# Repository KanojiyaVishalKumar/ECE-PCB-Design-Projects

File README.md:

# ECE PCB Design Projects

## Overview

Welcome to my PCB Design Projects repository.

This repository contains a collection of electronic circuit and PCB designs created using **KiCad** as part of my learning journey in **Electronics and Communication Engineering (ECE)**.

The goal of these projects is to strengthen my understanding of:

* Schematic design
* PCB layout
* Component selection
* Circuit simulation
* PCB routing
* Power electronics
* Embedded systems
* Hardware design

Most of the projects currently focus on **PCB design and 3D visualization**. Future updates will include PCB fabrication, hardware testing, performance analysis, and design optimization.

---

## Projects

| Status | Project                                |
| ------ | -------------------------------------- |
| ✅      | LM2596 Adjustable Buck Converter       |
| 🔨     | NE555 PWM LED Dimmer (Current Project) |
| 🔊     | LM386 Audio Amplifier                  |
| ⚡      | LM317 Adjustable Power Supply          |
| 🔌     | USB-to-UART Board                      |
| 🌡️    | Temperature Sensor Board               |
| 🖥️    | MCU + OLED Board                       |
| 📡     | ESP32 Sensor/Control Board             |
| 🏆     | Custom ESP32 Development Board         |

---

## Tools and Software

* KiCad
* PCB Editor
* Schematic Editor
* 3D Viewer

---

## Repository Structure

Each project contains:

* Circuit schematic
* PCB layout
* 3D PCB images
* Component information
* Project documentation

---

## Skills Demonstrated

* PCB design
* Analog electronics
* Power electronics
* Embedded systems
* Electronic circuit design
* Component placement
* PCB routing
* Design rule checking (DRC)

---

## Future Goals

* Fabricate the designed PCBs
* Test the hardware
* Improve power efficiency
* Optimize PCB layouts
* Expand the repository with more advanced projects

---

## Connect With Me

I regularly share my electronics projects and learning progress through GitHub and LinkedIn.

Feedback, suggestions, and collaboration are always welcome.

---

**Designed by:**  Kanojiya Vishal Kumar

**Branch:** Electronics and Communication Engineering (ECE)

**Software Used:** KiCad 10.0

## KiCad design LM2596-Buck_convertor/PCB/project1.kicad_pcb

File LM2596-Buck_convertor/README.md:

# LM2596 Adjustable Buck Converter

## Overview

This project presents the PCB design of an **LM2596-based adjustable buck converter** developed using **KiCad**.

A buck converter is a DC-to-DC power converter that efficiently reduces a higher input voltage to a lower output voltage while minimizing power loss. This design focuses on creating a compact, adjustable, and efficient power supply suitable for electronics prototyping and embedded system applications.

---

## Project Objectives

* Design an adjustable DC-DC buck converter
* Develop the complete schematic in KiCad
* Create a compact PCB layout
* Improve PCB routing and component placement skills
* Generate a 3D visualization of the final PCB

---

## Features

* Adjustable output voltage
* High-efficiency DC-to-DC conversion
* Compact PCB design
* Through-hole and standard components
* 3D PCB model

---

## Components Used

* LM2596 switching regulator
* Inductor
* Schottky diode
* Input capacitor
* Output capacitor
* Potentiometer
* Input connector
* Output connector
* Status LED

---

## PCB Design Process

1. Circuit design
2. Schematic capture
3. Footprint assignment
4. Component placement
5. PCB routing
6. Design rule checking (DRC)
7. 3D model generation

---

## Project Files

```text
LM2596-Adjustable-Buck-Converter
│
├── README.md
├── Schematic
├── PCB
└── Images
    ├── Schematic.png
    ├── PCB_Layout.png
    ├── 3D_Front.png
    └── 3D_Back.png
```

---

## Learning Outcomes

This project improved my understanding of:

* Switching regulators
* Power electronics
* PCB design principles
* Component placement
* PCB routing
* Electronic design automation (EDA) tools

---

## Future Improvements

* PCB fabrication
* Hardware testing
* Efficiency analysis
* Thermal analysis
* Design optimization

---

## Software Used

* KiCad

---

**Designed by Kanojiya Vishal Kumar**

**Electronics and Communication Engineering (ECE)**

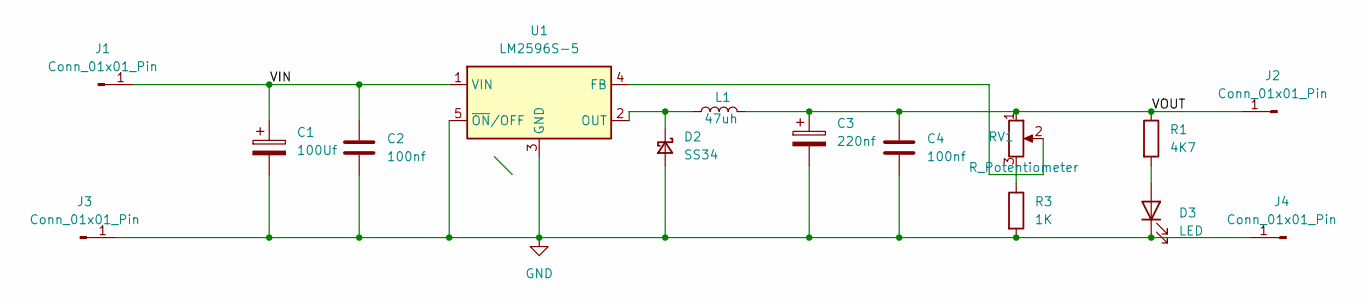
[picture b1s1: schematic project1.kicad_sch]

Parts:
C1: 100Uf; CP_Elec_8x10
C2, C4: 100nf; C_0603_1608Metric
C3: 220nf; CP_Elec_8x10
D2: SS34; D_SMA
D3: LED; LED_0603_1608Metric
J1, J2, J3, J4: Conn_01x01_Pin; PinSocket_1x01_P2.54mm_Vertical
L1: 47uh; L_0805_2012Metric
R1: 4K7; R_0603_1608Metric
R3: 1K; R_0603_1608Metric
RV1: R_Potentiometer; Potentiometer_Bourns_3296Y_Vertical
U1: LM2596S-5; TO-263-5_TabPin3

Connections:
/VIN: C1.1, C2.1, J1.1 (Pin_1_1), U1.1 (VIN)
/VOUT: C3.1, C4.1, J2.1 (Pin_1_1), L1.2, R1.1, RV1.1
GND: C1.2, C2.2, C3.2, C4.2, D2.2 (A), D3.1 (K), J3.1 (Pin_1_1), J4.1 (Pin_1_1), R3.2, U1.3 (GND), U1.5 (~ON/OFF)
unnamed: D2.1 (K), L1.1, U1.2 (OUT)
unnamed: D3.2 (A), R1.2
unnamed: R3.1, RV1.3
unnamed: RV1.2, U1.4 (FB)

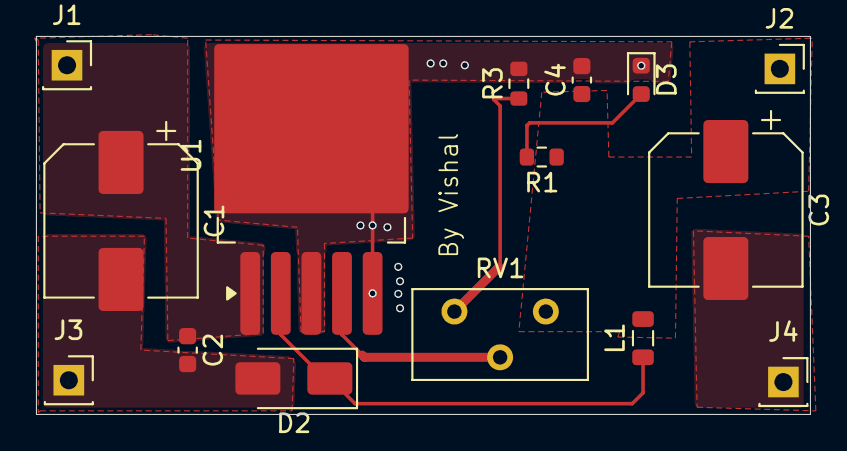
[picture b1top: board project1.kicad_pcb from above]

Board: 2 copper layers, 43.0 x 21.0 mm, 15 parts (0 on the bottom side), 7 nets.
